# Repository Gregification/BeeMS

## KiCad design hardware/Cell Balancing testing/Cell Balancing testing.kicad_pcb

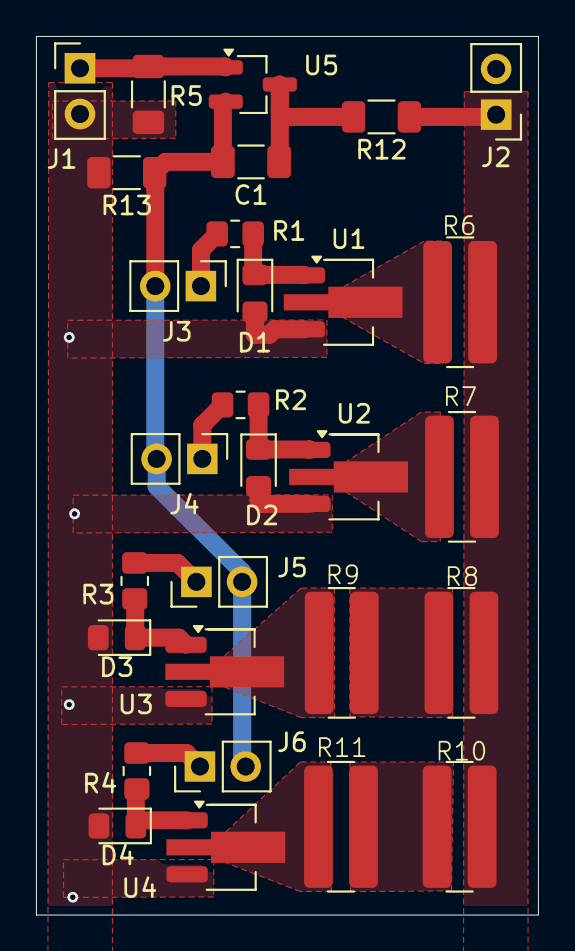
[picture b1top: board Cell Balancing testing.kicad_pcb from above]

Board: 2 copper layers, 27.9 x 48.8 mm, 29 parts (0 on the bottom side), 19 nets.

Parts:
C1: 100n; C_1206_3216Metric_Pad1.33x1.80mm_HandSolder
D1, D2, D3, D4: TS4148; D_0805_2012Metric_Pad1.15x1.40mm_HandSolder
J1: pwm; PinHeader_1x02_P2.54mm_Vertical
J2: cell; PinHeader_1x02_P2.54mm_Vertical
J3, J4, J5, J6: PinHeader_1x02_P2.54mm_Vertical
R1, R2, R3, R4: 226; R_0805_2012Metric_Pad1.20x1.40mm_HandSolder
R5: 4.99k; R_1206_3216Metric_Pad1.30x1.75mm_HandSolder
R6: 36; imperial wide resistor R_ 3264
R7, R8, R9: 20; imperial wide resistor R_ 3264
R10, R11: 16; imperial wide resistor R_ 3264
R12, R13: 100; R_1206_3216Metric_Pad1.30x1.75mm_HandSolder
U1, U2, U3, U4: 2PD2150-QX; SOT-89-3_Handsoldering
U5: DMN62D0U; SOT-23_Handsoldering

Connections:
/PWM: J1.1, R5.2, U5.1 (G)
/Rb: C1.2, J3.2, J4.2, J5.2, J6.2, R13.1, U5.2 (S)
/cell+: J2.1, R6.2, R7.2, R8.2, R10.2, R12.1
GND: D1.2 (A), D2.2 (A), D3.2 (A), D4.2 (A), J1.2, J2.2, R5.1, R13.2, U1.3 (E), U2.3 (E), U3.3 (E), U4.3 (E)
unnamed: D1.1 (K), R1.1, U1.1 (B)
unnamed: D2.1 (K), R2.1, U2.1 (B)
unnamed: D3.1 (K), R3.1, U3.1 (B)
unnamed: D4.1 (K), R4.1, U4.1 (B)
unnamed: J3.1, R1.2
unnamed: J4.1, R2.2
unnamed: J5.1, R3.2
unnamed: J6.1, R4.2
unnamed: R8.1, R9.2
unnamed: R10.1, R11.2
unnamed: R6.1, U1.2 (C)
unnamed: R7.1, U2.2 (C)
unnamed: R9.1, U3.2 (C)
unnamed: R11.1, U4.2 (C)
unnamed: C1.1, R12.2, U5.3 (D)

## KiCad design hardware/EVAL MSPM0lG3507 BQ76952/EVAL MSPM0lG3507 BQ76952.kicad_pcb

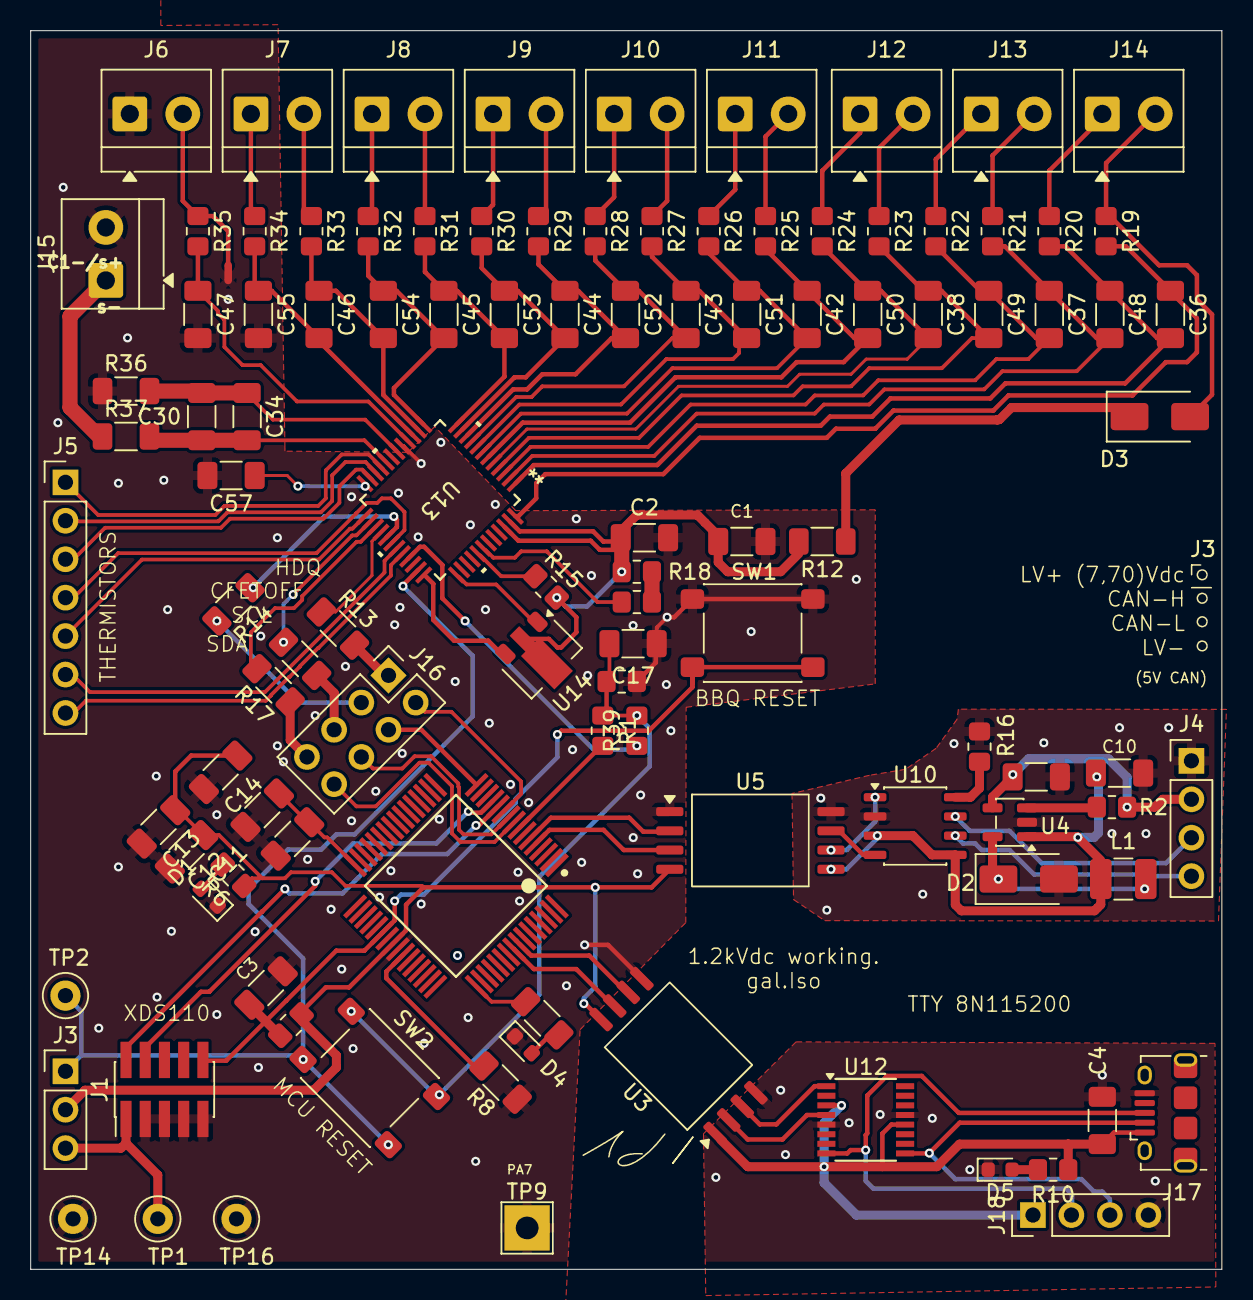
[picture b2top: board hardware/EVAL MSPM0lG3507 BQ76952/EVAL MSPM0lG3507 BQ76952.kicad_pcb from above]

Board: 2 copper layers, 78.7 x 81.8 mm, 108 parts (0 on the bottom side), 100 nets.

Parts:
C1, C2, C6: 1u; C_1206_3216Metric_Pad1.33x1.80mm_HandSolder
C3, C17, C30: 100n; C_1206_3216Metric_Pad1.33x1.80mm_HandSolder
C4, C10, C14, C57: 10u; C_1206_3216Metric_Pad1.33x1.80mm_HandSolder
C5, C11, C12, C13, C36, C37, C38, C42, C43, C44, C45, C46, C47, C48, C49, C50, C51, C52, C53, C54, C55: 220n; C_1206_3216Metric_Pad1.33x1.80mm_HandSolder
C34: 100p; C_1206_3216Metric_Pad1.33x1.80mm_HandSolder
D1, D4, D5: LED; LED_0603_1608Metric
D2, D3: ES1D; D_SMA
J1: Conn_02x05_Odd_Even; PinHeader_2x05_P1.27mm_Vertical_SMD
J3: Conn_01x03_Pin; PinHeader_1x03_P2.54mm_Vertical
J4, J18: Conn_01x04_Socket; PinHeader_1x04_P2.54mm_Vertical
J5: Conn_01x07_Pin; PinHeader_1x07_P2.54mm_Vertical
J6, J7, J8, J9, J10, J11, J12, J13, J14, J15: Screw_Terminal_01x02; TerminalBlock_MetzConnect_Type059_RT06302HBWC_1x02_P3.50mm_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
J16: Conn_02x04_Odd_Even; PinHeader_2x04_P2.54mm_Vertical
J17: USB_B_Micro; USB_Micro-B_Amphenol_10118194-0001LF_Horizontal
L1: 22u; L_1210_3225Metric_Pad1.42x2.65mm_HandSolder
NT1: NetTie_2; NetTie-2_SMD_Pad0.5mm
R1, R6, R9, R10, R15, R18, R39: 3.32k; R_0805_2012Metric_Pad1.20x1.40mm_HandSolder
R2, R7, R11, R16: 97.6k; R_0805_2012Metric_Pad1.20x1.40mm_HandSolder
R3: 750; R_1206_3216Metric_Pad1.30x1.75mm_HandSolder
R4, R12, R13, R14, R17: 150; R_1206_3216Metric_Pad1.30x1.75mm_HandSolder
R8: 100k; R_1206_3216Metric_Pad1.30x1.75mm_HandSolder
R19, R20, R21, R22, R23, R24, R25, R26, R27, R28, R29, R30, R31, R32, R33, R34, R35: 24.9; R_0805_2012Metric_Pad1.20x1.40mm_HandSolder
R36, R37: 100; R_1206_3216Metric_Pad1.30x1.75mm_HandSolder
SW1, SW2: SW_Push; SW_SPST_PTS645Sx43SMTR92
TP1, TP2, TP14, TP16: TestPoint; TestPoint_Loop_D2.50mm_Drill1.0mm_LowProfile
TP9: TestPoint; TestPoint_THTPad_3.0x3.0mm_Drill1.5mm
U1: MCU-MSM0G3507SPM; MSPM0G3507-64-IPC_A
U3, U5: STISO620; SOIC-8_7.5x5.85mm_P1.27mm
U4: RAA211805; TSOT-23-5
U10: MCP2542FDxMF; JEITA_SOIC-8_3.9x4.9mm_P1.27mm
U12: FT230XS; SSOP-16_3.9x4.9mm_P0.635mm
U13: PBQ76952PFBT; BQ76952_PFB48_TEX
U14: FCX495; SOT-89-3

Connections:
+BATT: D3.2 (A), J14.2, R19.1
-BATT: C1.2, C2.2, C3.2, C5.2, C11.2, C12.2, C13.2, C14.2, C17.1, C47.2, C55.2, C57.2, D1.1 (K), D4.1 (K), J1.3, J1.5, J1.7, J1.9, J6.1, J15.2, NT1.2, R8.1, R11.1, R36.1, SW1.2, TP9.1, TP14.1, TP16.1, U1.41 (VSS), U3.5 (GND2), U5.1 (VDD1), U13.17 (VSS)
/BQ76952 16C/1N: J6.2, NT1.1, R35.1
/BQ76952 16C/1P: J7.1, R34.1
/BQ76952 16C/2P: J7.2, R33.1
/BQ76952 16C/3P: J8.1, R32.1
/BQ76952 16C/4P: J8.2, R31.1
/BQ76952 16C/5P: J9.1, R30.1
/BQ76952 16C/6P: J9.2, R29.1
/BQ76952 16C/7P: J10.1, R28.1
/BQ76952 16C/8P: J10.2, R27.1
/BQ76952 16C/9P: J11.1, R26.1
/BQ76952 16C/10P: J11.2, R25.1
/BQ76952 16C/11P: J12.1, R24.1
/BQ76952 16C/12P: J12.2, R23.1
/BQ76952 16C/13P: J13.1, R22.1
/BQ76952 16C/14P: J13.2, R21.1
/BQ76952 16C/15P: J14.1, R20.1
/BQ76952 16C/ALERT: J5.5, U13.25 (ALERT)
/BQ76952 16C/BAT: C1.1, C2.1, R12.2, R15.2, R18.2, U13.46 (CP1), U13.47 (BAT), U14.2
/BQ76952 16C/CFETOFF: R14.1, U13.29 (CFETOFF)
/BQ76952 16C/DCHG: J5.6, U13.31 (DCHG)
/BQ76952 16C/DDSG: J5.7, U13.32 (DDSG)
/BQ76952 16C/DFETOFF: J5.4, U13.30 (DFETOFF)
/BQ76952 16C/HDQ: R13.1, U13.28 (HDQ)
/BQ76952 16C/PACK-: J15.1, R37.1
/BQ76952 16C/RST_SHUT: R39.1, U13.33 (RST_SHUT)
/BQ76952 16C/SCL: R4.2, U13.26 (SCL)
/BQ76952 16C/SDA: R17.2, U13.27 (SDA)
/BQ76952 16C/TS1: J5.1, U13.21 (TS1)
/BQ76952 16C/TS2: J5.2, U13.22 (TS2)
/BQ76952 16C/TS3: J5.3, U13.23 (TS3)
/GLV interface/5v: C10.1, L1.2, U4.1 (VOUT), U5.5 (GND2), U10.3 (VDD), U10.5 (VIO)
/GLV interface/CAN_H: J4.3, U10.7 (CANH)
/GLV interface/CAN_L: J4.4, U10.6 (CANL)
/GLV interface/GLV+: C6.1, J4.2, R2.2, U4.4 (VIN)
/GLV interface/GLV-: C6.2, C10.2, D2.2 (A), J4.1, R16.1, U4.2 (GND), U5.8 (VDD2), U10.2 (VSS)
/UART_USB/5V: C4.1, J17.1 (VBUS), J18.1, R10.1, U3.1 (VDD1), U12.3 (VCCIO), U12.12 (VCC)
/UART_USB/GND: C4.2, D5.1 (K), J17.5 (GND), J18.4, U3.4 (GND1), U12.5 (GND), U12.13 (GND)
/XDS_3v_supply: J1.1, J3.3, TP1.1
unnamed: C17.2, R1.1, R11.2, R39.2, SW2.2
unnamed: D1.2 (A), R6.2
unnamed: D2.1 (K), L1.1, U4.5 (SW)
unnamed: D3.1 (K), R12.1
unnamed: D4.2 (A), R3.2
unnamed: D5.2 (A), R10.2
unnamed: J16.1, R13.2
unnamed: J16.3, R14.2
unnamed: J16.5, R4.1
unnamed: J16.7, R17.1
unnamed: J17.3 (D+), J18.2, U12.8 (USBDP)
unnamed: J17.2 (D-), J18.3, U12.9 (USBDM)
unnamed: R9.2, R18.1
unnamed: R8.2, U1.42 (PA2_ROSC)
unnamed: C5.1, C11.1, U1.32 (VCORE)
unnamed: R2.1, U4.3 (EN)
unnamed: U5.7 (TXB), U10.4 (RXD)
unnamed: R16.2, U10.8 (STBY)
unnamed: U5.6 (RXA), U10.1 (TXD)
unnamed: U3.2 (RXB), U12.4 (RXD)
unnamed: U3.3 (TXA), U12.1 (TXD)
unnamed: U13.37 (BREG), U14.1
unnamed: R15.1, U13.41 (LD)
unnamed: R9.1, U13.42 (PACK)
unnamed: C57.1, U13.24 (REG18)
unnamed: U13.36 (REGIN), U14.3
unnamed: C30.2, C34.2, R37.2, U13.20 (SRN)
unnamed: C30.1, C34.1, R36.2, U13.18 (SRP)
unnamed: C47.1, R35.2, U13.16 (VC0)
unnamed: C46.2, C55.1, R34.2, U13.15 (VC1)
unnamed: C46.1, C54.2, R33.2, U13.14 (VC2)
unnamed: C45.2, C54.1, R32.2, U13.13 (VC3)
unnamed: C45.1, C53.2, R31.2, U13.12 (VC4)
unnamed: C44.2, C53.1, R30.2, U13.11 (VC5)
unnamed: C44.1, C52.2, R29.2, U13.10 (VC6)
unnamed: C43.2, C52.1, R28.2, U13.9 (VC7)
unnamed: C43.1, C51.2, R27.2, U13.8 (VC8)
unnamed: C42.2, C51.1, R26.2, U13.7 (VC9)
unnamed: C42.1, C50.2, R25.2, U13.6 (VC10)
unnamed: C38.2, C50.1, R24.2, U13.5 (VC11)
unnamed: C38.1, C49.2, R23.2, U13.4 (VC12)
unnamed: C37.2, C49.1, R22.2, U13.3 (VC13)
unnamed: C37.1, C48.2, R21.2, U13.2 (VC14)
unnamed: C36.2, C48.1, R20.2, U13.1 (VC15)
unnamed: C36.1, R19.2, U13.48 (VC16)
PA7: R3.1, U1.49 (PA7)
PA10_UART0-TX_XDS: U1.56 (PA10), U3.7 (TXB)
PA11_UART0-RX_XDS: U1.57 (PA11), U3.6 (RXA)
PA12_CAN_TX: U1.5 (PA12_CAN_TX), U5.3 (TXA)
PA13_CAN_RX: U1.6 (PA13_CAN_RX), U5.2 (RXB)
PA15_BBQ_RESET: R1.2, U1.8 (PA15_A1_0)
PA16_SPI1_MISO: J16.8, U1.9 (PA16_A1_1)
PA17_SPI1_SCK: J16.6, U1.10 (PA17_A1_2)
PA18_SPI1_MOSI: J16.2, U1.11 (PA18_A1_3)
PA19_SWDIO: J1.2, U1.12 (PA19_SWDIO)
PA20_SWCLK: J1.4, U1.13 (PA20_SWCLK)
PB19_BBQ_CS: J16.4, U1.16 (PB19_A1_6)
RST_N: C3.1, J1.10, R7.1, SW1.1, U1.38 (RST_N)
VDD: C12.1, C13.1, C14.1, J3.2, R6.1, R7.2, U1.40 (VDD), U3.8 (VDD2), U5.4 (GND1)
onboard 3.3v src: J3.1, SW2.1, TP2.1, U13.35 (REG1)

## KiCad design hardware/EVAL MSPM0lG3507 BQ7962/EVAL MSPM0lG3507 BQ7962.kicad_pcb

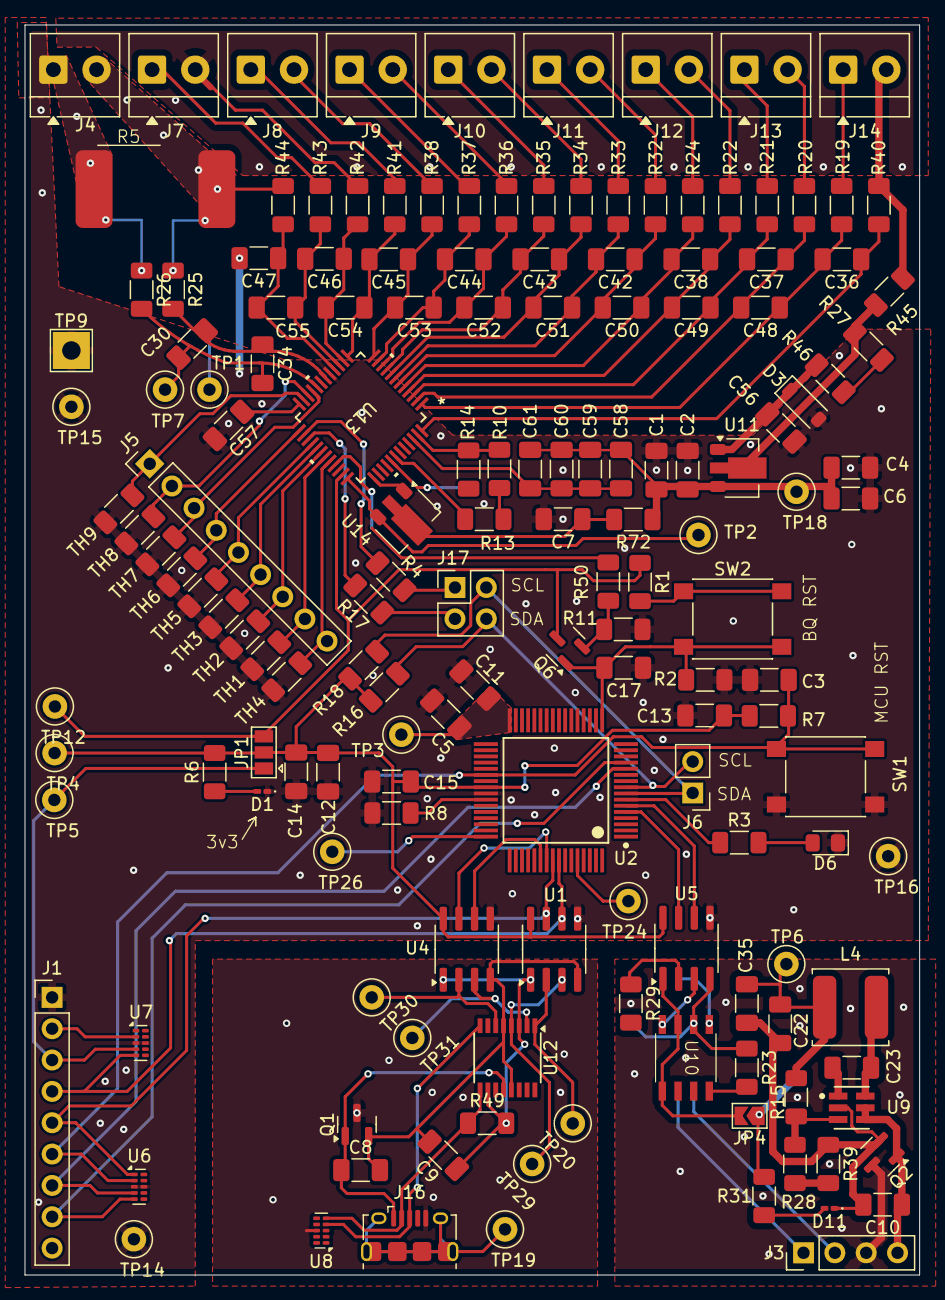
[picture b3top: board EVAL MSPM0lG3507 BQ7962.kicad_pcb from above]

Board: 2 copper layers, 72.5 x 101.3 mm, 160 parts (0 on the bottom side), 116 nets.

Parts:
C1, C2, C4, C6, C7, C10, C14, C35, C57: 10u; C_1206_3216Metric_Pad1.33x1.80mm_HandSolder
C3, C15, C17, C23, C30, C56, C58, C59, C60, C61: 100n; C_1206_3216Metric_Pad1.33x1.80mm_HandSolder
C5, C8, C9, C11, C12, C13, C22, C36, C37, C38, C42, C43, C44, C45, C46, C47, C48, C49, C50, C51, C52, C53, C54, C55: 220n; C_1206_3216Metric_Pad1.33x1.80mm_HandSolder
C34: 100p; C_1206_3216Metric_Pad1.33x1.80mm_HandSolder
D1, D11: LED; LED_0201_0603Metric_Pad0.64x0.40mm_HandSolder
D3: 36V; D_SOD-123
D6: LED; LED_0805_2012Metric_Pad1.15x1.40mm_HandSolder
J1, J5: Conn_01x09_Socket; PinHeader_1x09_P2.54mm_Vertical
J3: Conn_01x04_Pin; PinHeader_1x04_P2.54mm_Vertical
J4, J7, J8, J9, J10, J11, J12, J13, J14: Screw_Terminal_01x02; TerminalBlock_MetzConnect_Type059_RT06302HBWC_1x02_P3.50mm_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
J6: Conn_01x02_Pin; PinHeader_1x02_P2.54mm_Vertical
J16: USB_B_Micro; USB_Micro-B_Amphenol_10118194-0001LF_Horizontal
J17: Conn_02x02_Odd_Even; PinHeader_2x02_P2.54mm_Vertical
JP1: SolderJumper_3_Open; SolderJumper-3_P1.3mm_Open_Pad1.0x1.5mm
JP4: SolderJumper_2_Open; SolderJumper-2_P1.3mm_Open_TrianglePad1.0x1.5mm
L4: 100u; L_TDK_VLS6045EX_VLS6045AF
NT1: NetTie_2; NetTie-2_SMD_Pad0.5mm
Q1, Q2, Q6: 2N7002; SOT-23
R1, R10, R13, R14, R16, R18, R29, R49, R50: 4.99k; R_1206_3216Metric_Pad1.30x1.75mm_HandSolder
R2, R7, R11, R23: 49.9k; R_1206_3216Metric_Pad1.30x1.75mm_HandSolder
R3, R6, R31: 700; R_1206_3216Metric_Pad1.30x1.75mm_HandSolder
R4, R17: 150; R_1206_3216Metric_Pad1.30x1.75mm_HandSolder
R5: 1m; R_shunt_3921
R8, R15, R27, R46: 100k; R_1206_3216Metric_Pad1.30x1.75mm_HandSolder
R19, R20, R21, R22, R24, R32, R33, R34, R35, R36, R37, R38, R40, R41, R42, R43, R44: 50; R_1206_3216Metric_Pad1.30x1.75mm_HandSolder
R25, R26: 100; R_1206_3216Metric_Pad1.30x1.75mm_HandSolder
R28, R39: 9.53k; R_1206_3216Metric_Pad1.30x1.75mm_HandSolder
R45, R72: 200; R_1206_3216Metric_Pad1.30x1.75mm_HandSolder
SW1, SW2: SW_Push; SW_SPST_PTS645
TH1, TH2, TH3, TH4, TH5, TH6, TH7, TH8, TH9: Thermistor_US; R_1206_3216Metric_Pad1.30x1.75mm_HandSolder
TP1, TP2, TP3, TP4, TP5, TP6, TP7, TP12, TP14, TP15, TP16, TP18, TP19, TP20, TP24, TP26, TP29, TP30, TP31: TestPoint; TestPoint_Loop_D2.50mm_Drill1.0mm_LowProfile
TP9: TestPoint; TestPoint_THTPad_3.0x3.0mm_Drill1.5mm
U1, U4, U5: ISO7721D; SOIC-8_3.9x4.9mm_P1.27mm
U2: MCU-MSM0G3507SPM; MSPM0G3507-64-IPC_A
U6, U7, U8: TPD4E05U06DQA; USON-10_2.5x1.0mm_P0.5mm
U9: LMR51603XDBVR; DBV0006A-MFG-IPC_B
U10: MCP2542FDxMF; SOIC-8_4.9x6.0mm_P1.27mm
U11, U14: FCX495; SOT-89-3
U12: FT230XS; SSOP-16_3.9x4.9mm_P0.635mm
U13: PBQ76952PFBT; BQ76952_PFB48_TEX

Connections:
+BATT: J14.2, R40.1, R45.2
-BATT: C1.2, C2.2, C3.2, C4.2, C5.2, C6.2, C7.2, C11.2, C12.2, C13.2, C14.2, C15.2, C17.1, C47.2, C56.2, C57.2, D1.1 (K), D3.2 (A), D6.1 (K), J1.1, J4.1, R2.1, R5.1, R8.1, R11.1, R26.1, SW1.2, TH1.2, TH2.2, TH3.2, TH4.2, TH5.2, TH6.2, TH7.2, TH8.2, TH9.2, TP9.1, TP14.1, TP15.1, TP16.1, U1.5 (GND2), U2.41 (VSS), U4.5 (GND2), U5.5 (GND2), U6.3 (GND), U6.8 (GND), U7.3 (GND), U7.8 (GND), U13.17 (VSS)
/BQ76952 16C/1N: J4.2, R5.2, R25.1, R44.1
/BQ76952 16C/1P: J7.1, R43.1
/BQ76952 16C/2P: NT1.2, R42.1
/BQ76952 16C/3P: J8.1, R41.1
/BQ76952 16C/4P: J8.2, R38.1
/BQ76952 16C/5P: J9.1, R37.1
/BQ76952 16C/6P: J9.2, R36.1
/BQ76952 16C/7P: J10.1, R35.1
/BQ76952 16C/8P: J10.2, R34.1
/BQ76952 16C/9P: J11.1, R33.1
/BQ76952 16C/10P: J11.2, R32.1
/BQ76952 16C/11P: J12.1, R24.1
/BQ76952 16C/12P: J12.2, R22.1
/BQ76952 16C/13P: J13.1, R21.1
/BQ76952 16C/14P: J13.2, R20.1
/BQ76952 16C/15P: J14.1, R19.1
/BQ76952 16C/ALERT: J5.4, TH6.1, U13.25 (ALERT)
/BQ76952 16C/BAT: C1.1, C2.1, C4.1, C6.1, C58.1, C59.1, C60.1, C61.1, R10.2, R14.1, R72.1, TP18.1, U11.3, U13.47 (BAT)
/BQ76952 16C/CFETOFF: J5.6, TH3.1, U13.29 (CFETOFF)
/BQ76952 16C/DCHG: J5.8, TH1.1, U13.31 (DCHG)
/BQ76952 16C/DDSG: J5.9, TH4.1, U13.32 (DDSG)
/BQ76952 16C/DFETOFF: J5.7, TH2.1, U13.30 (DFETOFF)
/BQ76952 16C/HDQ: J5.5, TH5.1, U13.28 (HDQ)
/BQ76952 16C/LD: R14.2, U13.41 (LD)
/BQ76952 16C/PACK: R13.1, U13.42 (PACK)
/BQ76952 16C/RST_SHUT: R50.1, U13.33 (RST_SHUT)
/BQ76952 16C/SCL: R4.1, U13.26 (SCL)
/BQ76952 16C/SDA: R17.2, U13.27 (SDA)
/BQ76952 16C/TS1: J5.3, TH7.1, U13.21 (TS1)
/BQ76952 16C/TS2: J5.2, TH8.1, U13.22 (TS2)
/BQ76952 16C/TS3: J5.1, TH9.1, U13.23 (TS3)
/GLV CAN TRX/5v: JP4.2 (B), U5.1 (VCC1), U10.3 (VDD), U10.5 (VIO)
/GLV CAN TRX/-GLV: R23.1, R29.2, U5.4 (GND1), U10.2 (VSS)
/GLV CAN TRX/CAN_H: J3.2, U10.7 (CANH)
/GLV CAN TRX/CAN_L: J3.1, U10.6 (CANL)
/GLV CAN TRX/CAN_VDD: C10.1, J3.4, Q2.1 (G), U9.4 (EN), U9.5 (VIN)
/GLV CAN TRX/CAN_VSS: J3.3, Q2.3 (D)
/UART_USB/D+: J16.3 (D+), U8.4 (D2+), U12.8 (USBDP)
/UART_USB/D-: J16.2 (D-), R49.1, U8.5 (D2-), U12.9 (USBDM)
/UART_USB/GND: J16.5 (GND), Q1.3 (D), U8.3 (GND), U8.8 (GND)
/UART_USB/VBUS_5v: C8.1, J16.1 (VBUS), Q1.1 (G), U12.12 (VCC)
/XDS_3v_supply: J1.3, JP1.1 (A), TP5.1, U7.4 (D2+)
/XDS_5v_supply: J1.2, U7.2 (D1-)
unnamed: C7.1, R72.2, U14.2
unnamed: C56.1, D3.1 (K), R46.1, U11.1
unnamed: D1.2 (A), R6.1
unnamed: D6.2 (A), R3.2
unnamed: D11.2 (A), R31.2
unnamed: C10.2, C22.2, C35.2, D11.1 (K), Q2.2 (S), R39.1, U9.2 (GND)
unnamed: J7.2, NT1.1
unnamed: J16.6 (Shield), TP19.1
unnamed: J17.1, R4.2
unnamed: J17.3, R17.1
unnamed: C22.1, C35.1, JP4.1 (A), L4.2, R15.2, R31.1, TP6.1
unnamed: C8.2, C9.2, Q1.2 (S), U1.4 (GND1), U4.4 (GND1), U12.5 (GND), U12.13 (GND)
unnamed: Q6.2 (S), R11.2, R50.2
unnamed: R1.2, SW2.1
unnamed: R10.1, R13.2
unnamed: R27.1, R46.2
unnamed: R27.2, R45.1, U11.2
unnamed: R28.1, R39.2
unnamed: TP29.1, U1.3 (INB), U12.4 (RXD)
unnamed: TP20.1, U1.2 (OUTA), U12.1 (TXD)
unnamed: C9.1, R49.2, U1.1 (VCC1), U4.1 (VCC1), U12.3 (VCCIO), U12.10 (3V3OUT)
unnamed: R8.2, U2.42 (PA2_ROSC)
unnamed: TP26.1, U2.48 (PB1)
unnamed: TP24.1, U2.60 (PB8)
unnamed: C5.1, C11.1, TP3.1, U2.32 (VCORE)
unnamed: C23.1, U9.1 (CB)
unnamed: R15.1, R28.2, U9.3 (FB)
unnamed: C23.2, L4.1, U9.6 (SW)
unnamed: U5.3 (INB), U10.4 (RXD)
unnamed: R23.2, U10.8 (STBY)
unnamed: R29.1, U5.2 (OUTA), U10.1 (TXD)
unnamed: TP30.1, U4.2 (OUTA), U12.6 (~CTS)
unnamed: TP31.1, U4.3 (INB), U12.2 (~RTS)
unnamed: U13.37 (BREG), U14.1
unnamed: C58.2, C59.2, C60.2, C61.2, U13.46 (CP1)
unnamed: C57.1, U13.24 (REG18)
unnamed: TP2.1, U13.36 (REGIN), U14.3
unnamed: C30.2, C34.2, R26.2, TP7.1, U13.20 (SRN)
unnamed: C30.1, C34.1, R25.2, TP1.1, U13.18 (SRP)
unnamed: C47.1, C55.2, R44.2, U13.16 (VC0)
unnamed: C46.2, C55.1, R43.2, U13.15 (VC1)
unnamed: C46.1, C54.2, R42.2, U13.14 (VC2)
unnamed: C45.2, C54.1, R41.2, U13.13 (VC3)
unnamed: C45.1, C53.2, R38.2, U13.12 (VC4)
unnamed: C44.2, C53.1, R37.2, U13.11 (VC5)
unnamed: C44.1, C52.2, R36.2, U13.10 (VC6)
unnamed: C43.2, C52.1, R35.2, U13.9 (VC7)
unnamed: C43.1, C51.2, R34.2, U13.8 (VC8)
unnamed: C42.2, C51.1, R33.2, U13.7 (VC9)
unnamed: C42.1, C50.2, R32.2, U13.6 (VC10)
unnamed: C38.2, C50.1, R24.2, U13.5 (VC11)
unnamed: C38.1, C49.2, R22.2, U13.4 (VC12)
unnamed: C37.2, C49.1, R21.2, U13.3 (VC13)
unnamed: C37.1, C48.2, R20.2, U13.2 (VC14)
unnamed: C36.2, C48.1, R19.2, U13.1 (VC15)
unnamed: C36.1, R40.2, U13.48 (VC16)
PA8_UART0-RTS: U2.54 (PA8), U4.6 (OUTB)
PA9_UART0-CTS: U2.55 (PA9), U4.7 (INA)
PA10_UART0-TX_XDS: J1.5, U1.7 (INA), U2.56 (PA10), U6.1 (D1+)
PA11_UART0-RX_XDS: J1.4, U1.6 (OUTB), U2.57 (PA11), U7.5 (D2-)
PA12_CAN_TX: U2.5 (PA12_CAN_TX), U5.7 (INA)
PA13_CAN_RX: U2.6 (PA13_CAN_RX), U5.6 (OUTB)
PA14: R3.1, U2.7 (PA14)
PA15_I2C1_SCL: J6.1, J17.2, R16.1, U2.8 (PA15_A1_0)
PA16_I2C1_SDA: J6.2, J17.4, R18.2, U2.9 (PA16_A1_1)
PA19_SWDIO: J1.7, U2.12 (PA19_SWDIO), U6.4 (D2+)
PA20_SWCLK: J1.8, U2.13 (PA20_SWCLK), U6.5 (D2-)
PA21_A1_7_VREF-: C17.2, Q6.1 (G), R2.2, SW2.2, U2.17 (PA21_A1_7_VREF-)
RST_N: C3.1, J1.6, R7.2, SW1.1, U2.38 (RST_N), U6.2 (D1-)
VDD: C12.1, C13.1, C14.1, C15.1, JP1.2 (C), R6.2, R7.1, R16.2, R18.1, TP4.1, U1.8 (VCC2), U2.40 (VDD), U4.8 (VCC2), U5.8 (VCC2)
onboard 3.3v src: JP1.3 (B), Q6.3 (D), R1.1, TP12.1, U13.35 (REG1)

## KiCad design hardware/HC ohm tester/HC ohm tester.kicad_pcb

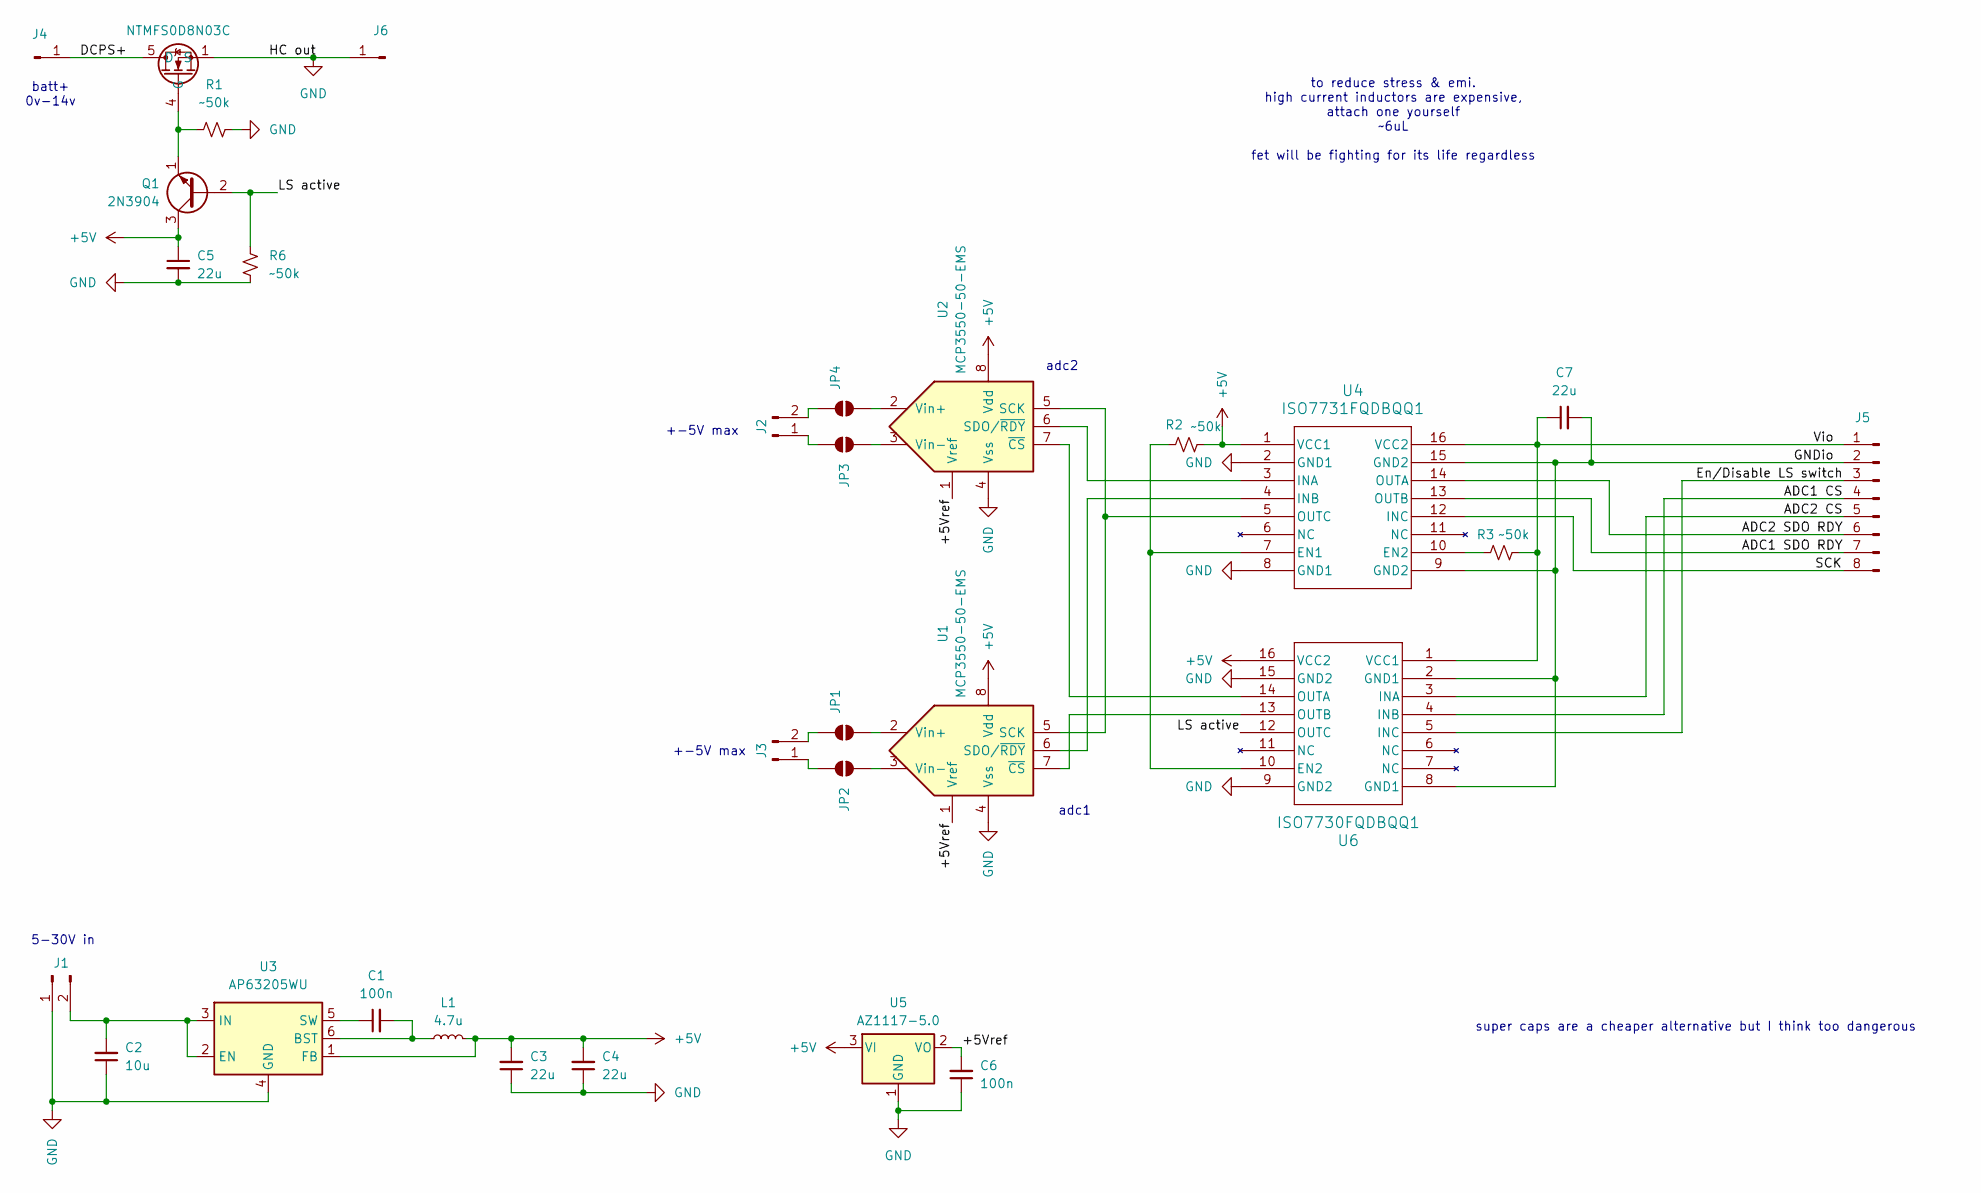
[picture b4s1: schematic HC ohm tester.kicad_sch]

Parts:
C1, C6: 100n; C_1206_3216Metric_Pad1.33x1.80mm_HandSolder
C2: 10u; C_1206_3216Metric_Pad1.33x1.80mm_HandSolder
C3, C4, C5, C7: 22u; C_1206_3216Metric_Pad1.33x1.80mm_HandSolder
J1, J2, J3: Conn_01x02_Pin; PinHeader_1x02_P2.54mm_Vertical
J4: DCPS+; MountingHole_3mm_Pad_TopBottom
J5: Conn_01x08_Pin; PinHeader_1x08_P2.54mm_Vertical
J6: MountingHole_3mm_Pad_TopBottom
JP1, JP2, JP3, JP4: SolderJumper_2_Open; SolderJumper-2_P1.3mm_Open_RoundedPad1.0x1.5mm
L1: 4.7u; L_0603_1608Metric_Pad1.05x0.95mm_HandSolder
Q1: 2N3904; TO-92_Inline
Q3: NTMFS0D8N03C; ONSemi_SO-8FL_488AA
R1, R2, R3, R6: ~50k; R_1206_3216Metric_Pad1.30x1.75mm_HandSolder
U1, U2: MCP3550-50-EMS; MSOP-8_3x3mm_P0.65mm
U3: AP63205WU; TSOT-23-6
U4: ISO7731FQDBQQ1; DBQ16_TEX-M
U5: AZ1117-5.0; SOT-223-3_TabPin2
U6: ISO7730FQDBQQ1; DBQ16_TEX-M

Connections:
+5V: C3.2, C4.2, C5.1, L1.2, Q1.3 (C), R2.1, U1.8 (Vdd), U2.8 (Vdd), U3.1 (FB), U4.1 (VCC1), U5.3 (VI), U6.16 (VCC2)
/+5Vref: C6.2, U1.1 (Vref), U2.1 (Vref), U5.2 (VO)
/ADC1 CS: J5.4, U6.4 (INB)
/ADC1 SDO RDY: J5.7, U4.13 (OUTB)
/ADC2 CS: J5.5, U6.3 (INA)
/ADC2 SDO RDY: J5.6, U4.14 (OUTA)
/DCPS+: J4.1, Q3.5 (D)
/En/Disable HS switch: J5.3, U6.5 (INC)
/GNDio: C7.2, J5.2, U4.9 (GND2), U4.15 (GND2), U6.2 (GND1), U6.8 (GND1)
/HS active: Q1.2 (B), R6.2, U6.12 (OUTC)
/SCK: J5.8, U4.12 (INC)
/Vio: C7.1, J5.1, R3.1, U4.16 (VCC2), U6.1 (VCC1)
GND: C2.1, C3.1, C4.1, C5.2, C6.1, J1.1, J6.1, Q3.1 (S), Q3.2 (S), Q3.3 (S), R1.2, R6.1, U1.4 (Vss), U2.4 (Vss), U3.4 (GND), U4.2 (GND1), U4.8 (GND1), U5.1 (GND), U6.9 (GND2), U6.15 (GND2)
unnamed: C2.2, J1.2, U3.2 (EN), U3.3 (IN)
unnamed: J2.1, JP3.1 (A)
unnamed: J2.2, JP4.2 (B)
unnamed: J3.1, JP2.1 (A)
unnamed: J3.2, JP1.2 (B)
unnamed: JP1.1 (A), U1.2 (Vin+)
unnamed: JP2.2 (B), U1.3 (Vin-)
unnamed: JP3.2 (B), U2.3 (Vin-)
unnamed: JP4.1 (A), U2.2 (Vin+)
unnamed: Q1.1 (E), Q3.4 (G), R1.1
unnamed: U1.5 (SCK), U2.5 (SCK), U4.5 (OUTC)
unnamed: U1.6 (SDO/~RDY), U4.4 (INB)
unnamed: U1.7 (~CS), U6.13 (OUTB)
unnamed: U2.6 (SDO/~RDY), U4.3 (INA)
unnamed: U2.7 (~CS), U6.14 (OUTA)
unnamed: C1.2, L1.1, U3.6 (BST)
unnamed: C1.1, U3.5 (SW)
unnamed: R2.2, U4.7 (EN1), U6.10 (EN2)
unnamed: R3.2, U4.10 (EN2)

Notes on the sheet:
+-5V max
adc1
batt+ 0v-14v
adc2
super caps are a cheaper alternative but I think too dangerous
to reduce stress & emi. high current inductors are expensive, attach one yourself ~6uL fet will be fighting for its life regardless
5-30V in

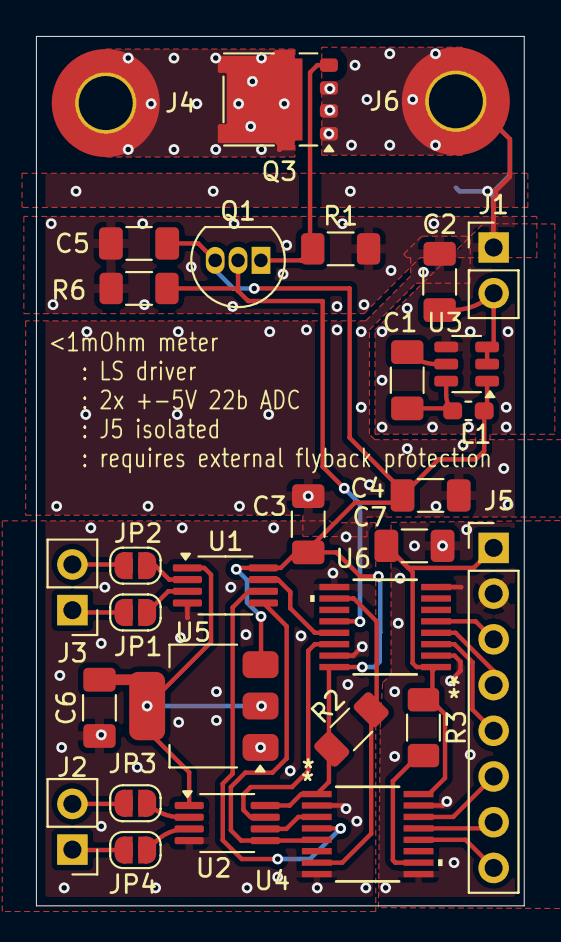
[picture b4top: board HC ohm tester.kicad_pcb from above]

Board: 2 copper layers, 27.1 x 48.3 mm, 30 parts (0 on the bottom side), 32 nets.

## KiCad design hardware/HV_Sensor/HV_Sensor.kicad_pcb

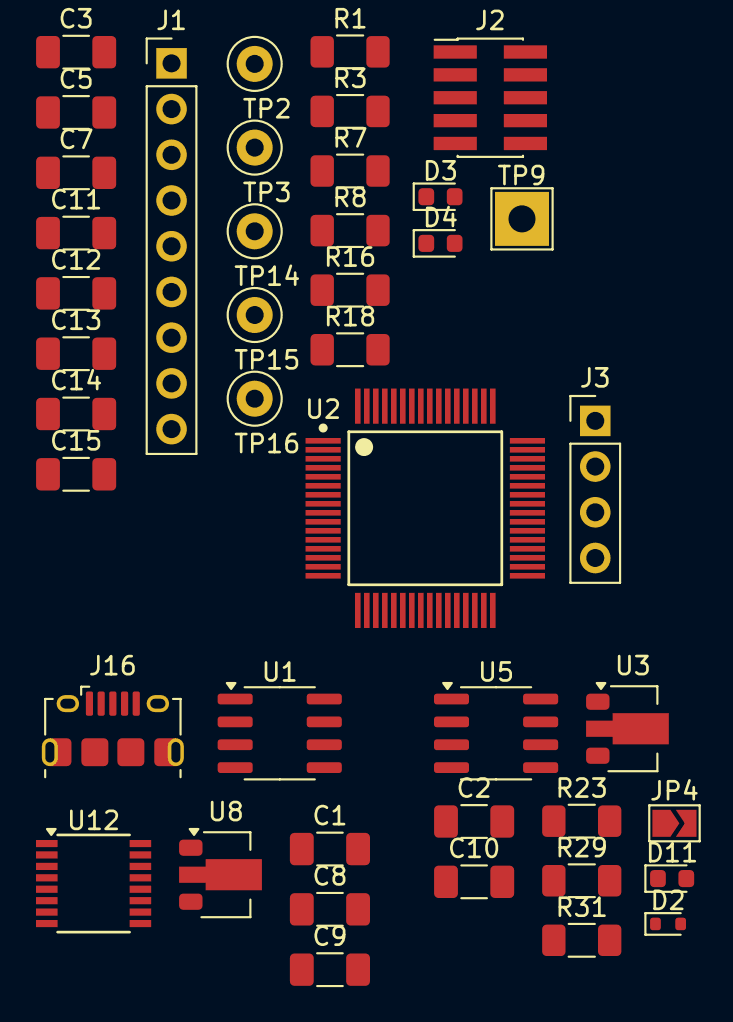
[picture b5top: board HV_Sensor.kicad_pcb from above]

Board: 2 copper layers, 43 parts (0 on the bottom side), 31 nets, no tracks yet.

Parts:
C1, C2, C8, C10, C14: 10u; C_1206_3216Metric_Pad1.33x1.80mm_HandSolder
C3, C15: 100n; C_1206_3216Metric_Pad1.33x1.80mm_HandSolder
C5, C7, C9, C11, C12, C13: 220n; C_1206_3216Metric_Pad1.33x1.80mm_HandSolder
D2: 1N4148WT; D_SOD-523
D3, D4, D11: LED; LED_0603_1608Metric
J1: Conn_01x09_Socket; PinHeader_1x09_P2.54mm_Vertical
J2: Conn_02x05_Odd_Even; PinHeader_2x05_P1.27mm_Vertical_SMD
J3: Conn_01x04_Pin; PinHeader_1x04_P2.54mm_Vertical
J16: USB_B_Micro; USB_Micro-B_Amphenol_10118194-0001LF_Horizontal
JP4: SolderJumper_2_Open; SolderJumper-2_P1.3mm_Open_TrianglePad1.0x1.5mm
R1, R3, R31: 750; R_1206_3216Metric_Pad1.30x1.75mm_HandSolder
R7, R23: 49.9k; R_1206_3216Metric_Pad1.30x1.75mm_HandSolder
R8: 100k; R_1206_3216Metric_Pad1.30x1.75mm_HandSolder
R16, R18, R29: 4.99k; R_1206_3216Metric_Pad1.30x1.75mm_HandSolder
TP2, TP3, TP14, TP15, TP16: TestPoint; TestPoint_Loop_D2.50mm_Drill1.0mm_LowProfile
TP9: TestPoint; TestPoint_THTPad_3.0x3.0mm_Drill1.5mm
U1, U5: ISO7721D; SOIC-8_3.9x4.9mm_P1.27mm
U2: MCU-MSM0G3507SPM; MSPM0G3507-64-IPC_A
U3, U8: L78L05_SOT89; SOT-89-3
U12: FT230XS; SSOP-16_3.9x4.9mm_P0.635mm

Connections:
/GLV CAN TRX/5v: JP4.2 (B), U5.1 (VCC1)
/GLV CAN TRX/-GLV: C2.2, C10.2, D11.1 (K), J3.3, R23.1, R29.2, U3.2 (GND), U5.4 (GND1)
/GLV CAN TRX/CAN_VDD: D2.2 (A), J3.4
GND: C3.2, C5.2, C7.2, C11.2, C12.2, C13.2, C14.2, C15.2, D3.1 (K), D4.1 (K), J1.1, J2.3, J2.5, J2.7, J2.9, R8.1, TP9.1, TP14.1, TP15.1, TP16.1, U1.5 (GND2), U2.41 (VSS), U5.5 (GND2)
unnamed: C10.1, D2.1 (K), U3.3 (IN)
unnamed: D3.2 (A), R1.1
unnamed: D4.2 (A), R3.2
unnamed: D11.2 (A), R31.2
unnamed: J16.3 (D+), U12.8 (USBDP)
unnamed: J16.2 (D-), U12.9 (USBDM)
unnamed: C1.2, C8.2, C9.2, J16.5 (GND), U1.4 (GND1), U8.2 (GND), U12.5 (GND), U12.13 (GND)
unnamed: C1.1, J16.1 (VBUS), U8.3 (IN)
unnamed: C2.1, JP4.1 (A), R31.1, U3.1 (OUT)
unnamed: U1.3 (INB), U12.1 (TXD)
unnamed: U1.2 (OUTA), U12.4 (RXD)
unnamed: C8.1, C9.1, U1.1 (VCC1), U8.1 (OUT), U12.3 (VCCIO), U12.12 (VCC)
unnamed: R8.2, U2.42 (PA2_ROSC)
unnamed: TP2.1, U2.64 (PB12)
unnamed: C5.1, C11.1, TP3.1, U2.32 (VCORE)
unnamed: R29.1, U5.2 (OUTA)
PA10_UART0-TX_XDS: J1.5, U1.7 (INA), U2.56 (PA10)
PA11_UART0-RX_XDS: J1.4, U1.6 (OUTB), U2.57 (PA11)
PA12_CAN_TX: U2.5 (PA12_CAN_TX), U5.7 (INA)
PA13_CAN_RX: U2.6 (PA13_CAN_RX), U5.6 (OUTB)
PA14: R3.1, U2.7 (PA14)
PA15_I2C1_SCL: R16.1, U2.8 (PA15_A1_0)
PA16_I2C1_SDA: R18.2, U2.9 (PA16_A1_1)
PA19_SWDIO: J1.7, J2.2, U2.12 (PA19_SWDIO)
PA20_SWCLK: J1.8, J2.4, U2.13 (PA20_SWCLK)
RST_N: C3.1, J1.6, J2.10, R7.2, U2.38 (RST_N)
VDD: C7.1, C12.1, C13.1, C14.1, C15.1, R1.2, R7.1, R16.2, R18.1, U1.8 (VCC2), U2.40 (VDD), U5.8 (VCC2)
